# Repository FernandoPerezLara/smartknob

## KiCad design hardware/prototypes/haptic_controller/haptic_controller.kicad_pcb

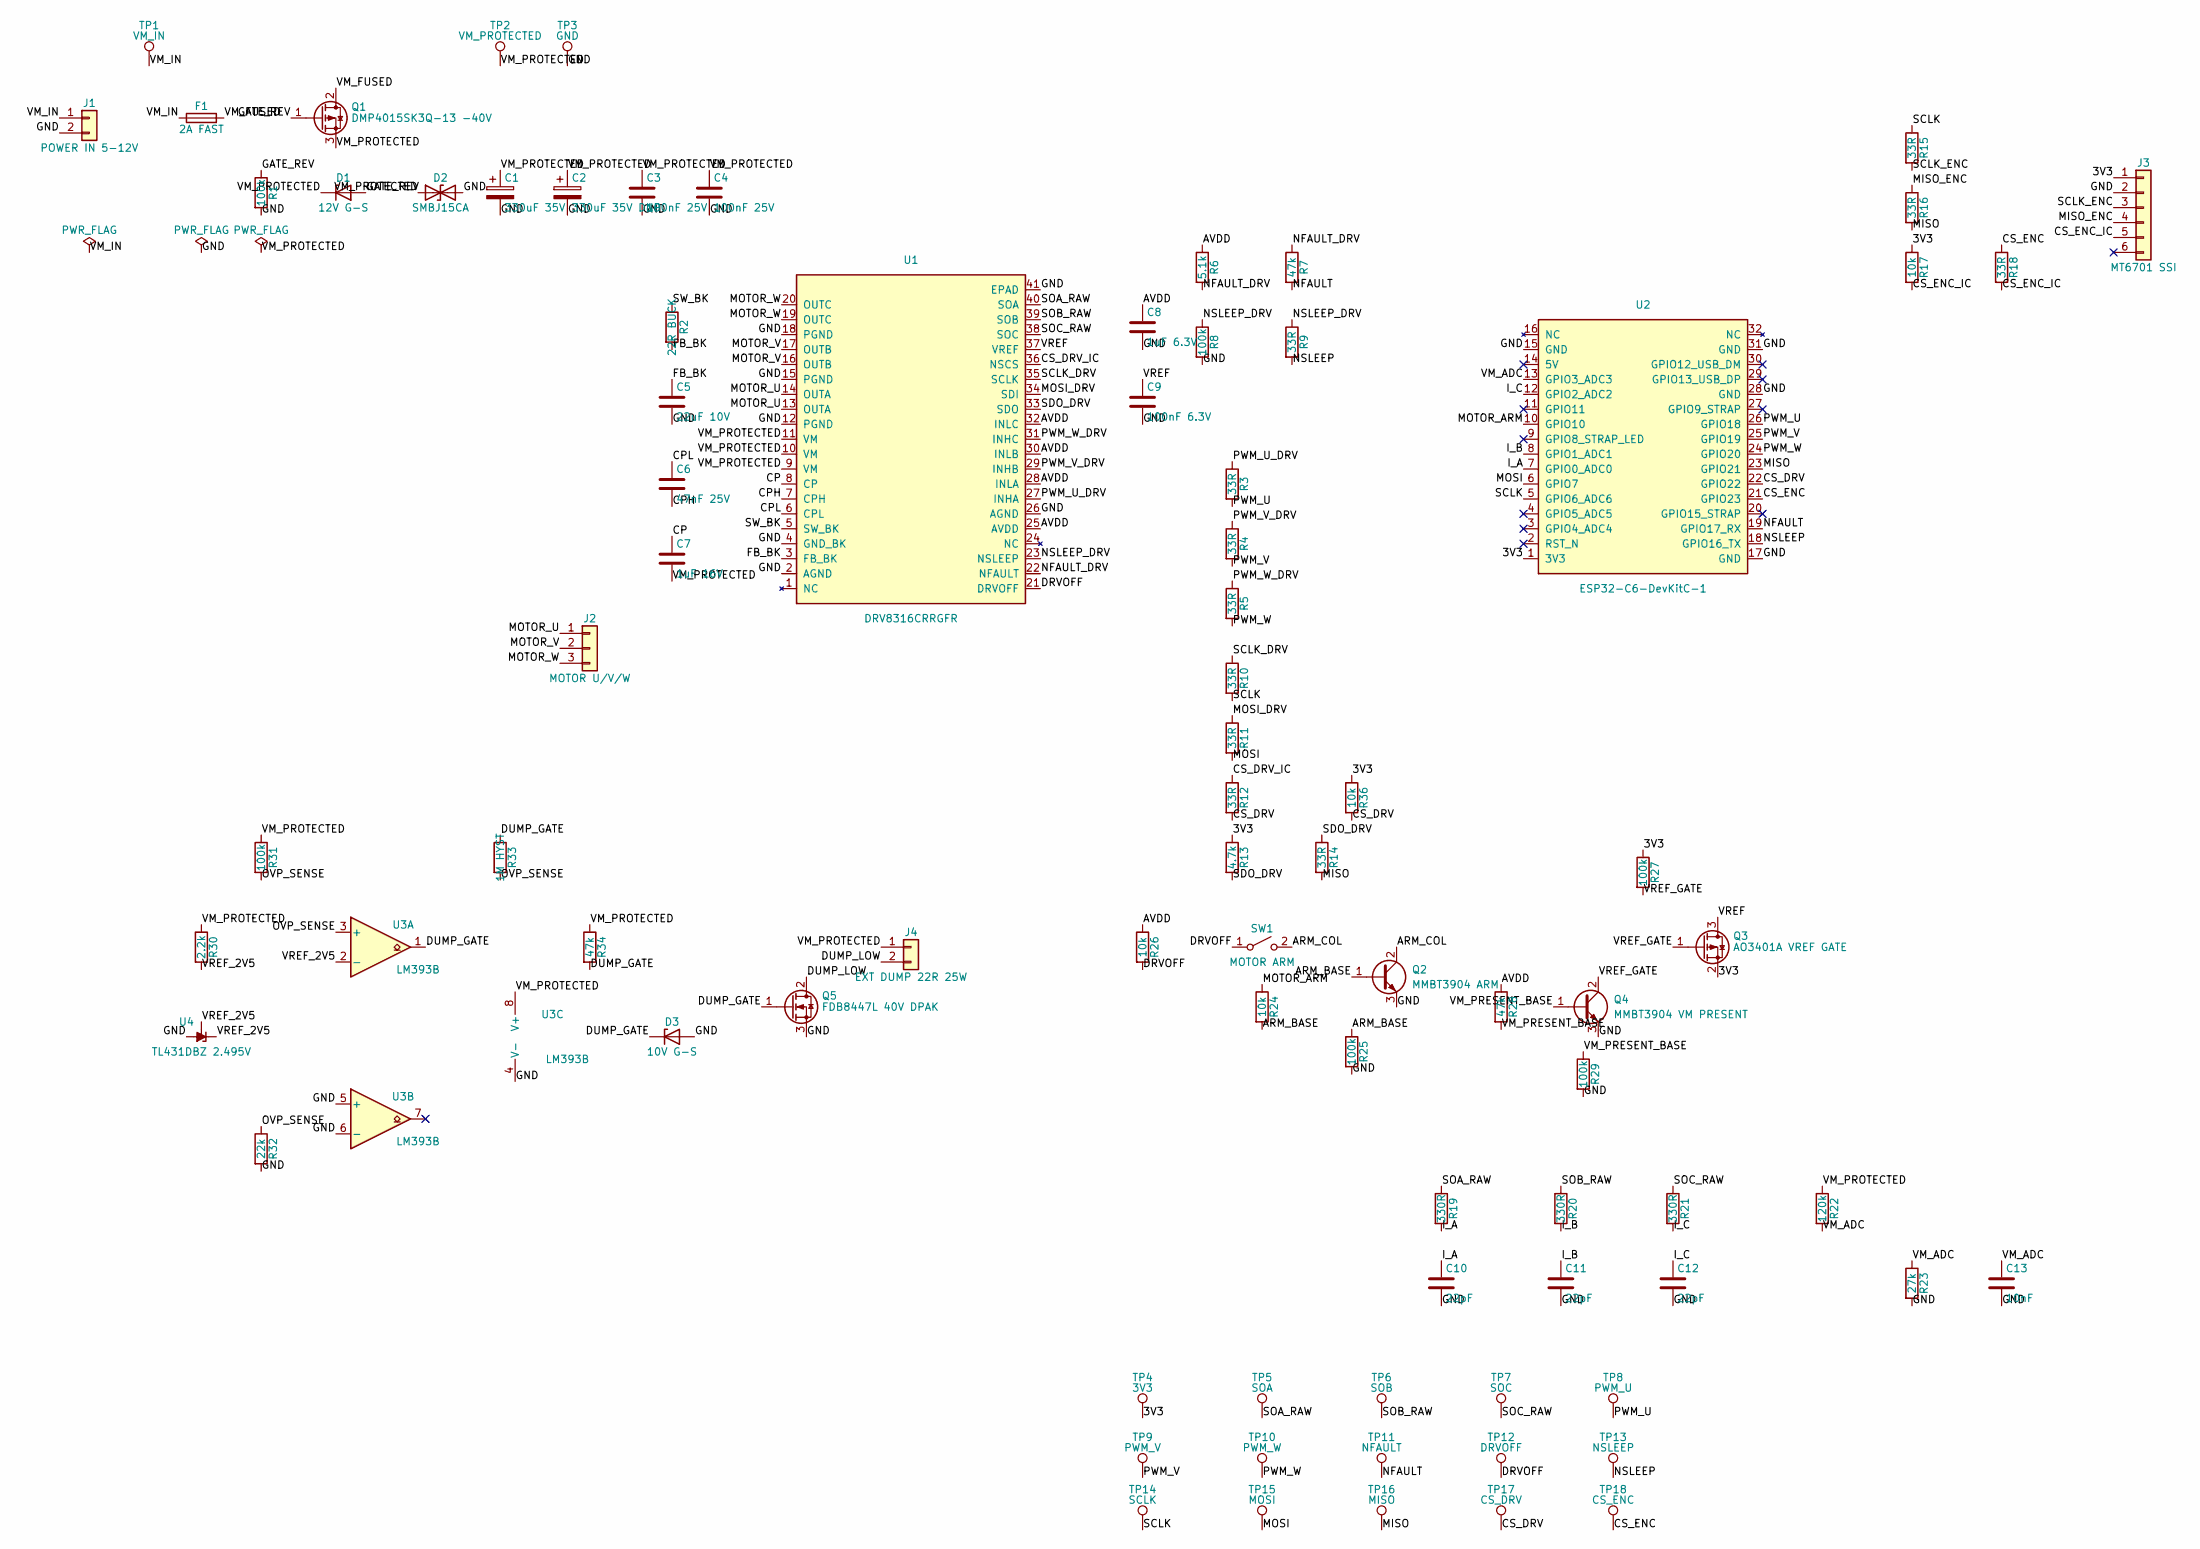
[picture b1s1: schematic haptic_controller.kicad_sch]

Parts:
C1: 330uF 35V; CP_Radial_D10.0mm_P5.00mm
C2: 330uF 35V DNP; CP_Radial_D10.0mm_P5.00mm
C3, C4: 100nF 25V; C_0603_1608Metric_Pad1.08x0.95mm_HandSolder
C5: 22uF 10V; C_0805_2012Metric_Pad1.18x1.45mm_HandSolder
C6: 47nF 25V; C_0603_1608Metric_Pad1.08x0.95mm_HandSolder
C7: 1uF 16V; C_0603_1608Metric_Pad1.08x0.95mm_HandSolder
C8: 1uF 6.3V; C_0603_1608Metric_Pad1.08x0.95mm_HandSolder
C9: 100nF 6.3V; C_0603_1608Metric_Pad1.08x0.95mm_HandSolder
C10, C11, C12: 22pF; C_0603_1608Metric_Pad1.08x0.95mm_HandSolder
C13: 10nF; C_0603_1608Metric_Pad1.08x0.95mm_HandSolder
D1: 12V G-S; D_SOD-123
D2: SMBJ15CA; D_SMA_Handsoldering
D3: 10V G-S; D_SOD-123
F1: 2A FAST; Fuseholder_Cylinder-5x20mm_Schurter_0031_8201_Horizontal_Op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
J1: POWER IN 5-12V; TerminalBlock_Phoenix_MKDS-1,5-2_1x02_P5.00mm_Horizontal
J2: MOTOR U/V/W; TerminalBlock_Phoenix_MKDS-1,5-3_1x03_P5.00mm_Horizontal
J3: MT6701 SSI; PinHeader_1x06_P2.54mm_Vertical
J4: EXT DUMP 22R 25W; TerminalBlock_Phoenix_MKDS-1,5-2_1x02_P5.00mm_Horizontal
Q1: DMP4015SK3Q-13 -40V; TO-252-2
Q2: MMBT3904 ARM; SOT-23
Q3: AO3401A VREF GATE; SOT-23
Q4: MMBT3904 VM PRESENT; SOT-23
Q5: FDB8447L 40V DPAK; TO-252-2
R1, R8, R25, R27, R29, R31: 100k; R_0603_1608Metric_Pad0.98x0.95mm_HandSolder
R2: 22R BUCK; R_0603_1608Metric_Pad0.98x0.95mm_HandSolder
R3, R4, R5, R9, R10, R11, R12, R14, R15, R16, R18: 33R; R_0603_1608Metric_Pad0.98x0.95mm_HandSolder
R6: 5.1k; R_0603_1608Metric_Pad0.98x0.95mm_HandSolder
R7, R28, R34: 47k; R_0603_1608Metric_Pad0.98x0.95mm_HandSolder
R13: 4.7k; R_0603_1608Metric_Pad0.98x0.95mm_HandSolder
R17, R24, R26, R36: 10k; R_0603_1608Metric_Pad0.98x0.95mm_HandSolder
R19, R20, R21: 330R; R_0603_1608Metric_Pad0.98x0.95mm_HandSolder
R22: 120k; R_0603_1608Metric_Pad0.98x0.95mm_HandSolder
R23: 27k; R_0603_1608Metric_Pad0.98x0.95mm_HandSolder
R30: 2.2k; R_0603_1608Metric_Pad0.98x0.95mm_HandSolder
R32: 22k; R_0603_1608Metric_Pad0.98x0.95mm_HandSolder
R33: 1M HYST; R_0603_1608Metric_Pad0.98x0.95mm_HandSolder
SW1: MOTOR ARM; SW_SPST_B3U-1000P
TP1: VM_IN; TestPoint_Plated_Hole_D2.0mm
TP2: VM_PROTECTED; TestPoint_Plated_Hole_D2.0mm
TP3: GND; TestPoint_Plated_Hole_D2.0mm
TP4: 3V3; TestPoint_Plated_Hole_D2.0mm
TP5: SOA; TestPoint_Plated_Hole_D2.0mm
TP6: SOB; TestPoint_Plated_Hole_D2.0mm
TP7: SOC; TestPoint_Plated_Hole_D2.0mm
TP8: PWM_U; TestPoint_Plated_Hole_D2.0mm
TP9: PWM_V; TestPoint_Plated_Hole_D2.0mm
TP10: PWM_W; TestPoint_Plated_Hole_D2.0mm
TP11: NFAULT; TestPoint_Plated_Hole_D2.0mm
TP12: DRVOFF; TestPoint_Plated_Hole_D2.0mm
TP13: NSLEEP; TestPoint_Plated_Hole_D2.0mm
TP14: SCLK; TestPoint_Plated_Hole_D2.0mm
TP15: MOSI; TestPoint_Plated_Hole_D2.0mm
TP16: MISO; TestPoint_Plated_Hole_D2.0mm
TP17: CS_DRV; TestPoint_Plated_Hole_D2.0mm
TP18: CS_ENC; TestPoint_Plated_Hole_D2.0mm
U1: DRV8316CRRGFR; DRV8316C_RGF40_Thermal
U2: ESP32-C6-DevKitC-1; ESP32-C6-DevKitC-1_Socket
U3: LM393B; SO-8_3.9x4.9mm_P1.27mm
U4: TL431DBZ 2.495V; SOT-23

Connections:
/3V3: J3.1, Q3.2 (S), R13.1, R17.1, R27.1, R36.1, TP4.1 (1_1), U2.1 (3V3)
/ARM_BASE: Q2.1 (B), R24.2, R25.1
/ARM_COL: Q2.2 (C), SW1.2 (B)
/AVDD: C8.1, R6.1, R26.1, R28.1, U1.25 (AVDD), U1.28 (INLA), U1.30 (INLB), U1.32 (INLC)
/CP: C7.1, U1.8 (CP)
/CPH: C6.2, U1.7 (CPH)
/CPL: C6.1, U1.6 (CPL)
/CS_DRV: R12.2, R36.2, TP17.1 (1_1), U2.22 (GPIO22)
/CS_DRV_IC: R12.1, U1.36 (NSCS)
/CS_ENC: R18.1, TP18.1 (1_1), U2.21 (GPIO23)
/CS_ENC_IC: J3.5, R17.2, R18.2
/DRVOFF: R26.2, SW1.1 (A), TP12.1 (1_1), U1.21 (DRVOFF)
/DUMP_GATE: D3.1 (K), Q5.1 (G), R33.1, R34.2, U3.1
/DUMP_LOW: J4.2, Q5.2 (D)
/FB_BK: C5.1, R2.2, U1.3 (FB_BK)
/GATE_REV: D1.2 (A), Q1.1 (G), R1.1
/GND: C1.2, C2.2, C3.2, C4.2, C5.2, C8.2, C9.2, C10.2, C11.2, C12.2, C13.2, D2.2 (A2), D3.2 (A), J1.2, J3.2, Q2.3 (E), Q4.3 (E), Q5.3 (S), R1.2, R8.2, R23.2, R25.2, R29.2, R32.2, TP3.1 (1_1), U1.2 (AGND), U1.4 (GND_BK), U1.12 (PGND), U1.15 (PGND), U1.18 (PGND), U1.26 (AGND), U1.41 (EPAD), U2.15 (GND), U2.17 (GND), U2.28 (GND), U2.31 (GND), U3.4 (V-), U3.5 (+), U3.6 (-), U4.3 (A)
/I_A: C10.1, R19.2, U2.7 (GPIO0_ADC0)
/I_B: C11.1, R20.2, U2.8 (GPIO1_ADC1)
/I_C: C12.1, R21.2, U2.12 (GPIO2_ADC2)
/MISO: R14.2, R16.2, TP16.1 (1_1), U2.23 (GPIO21)
/MISO_ENC: J3.4, R16.1
/MOSI: R11.2, TP15.1 (1_1), U2.6 (GPIO7)
/MOSI_DRV: R11.1, U1.34 (SDI)
/MOTOR_ARM: R24.1, U2.10 (GPIO10)
/MOTOR_U: J2.1, U1.13 (OUTA), U1.14 (OUTA)
/MOTOR_V: J2.2, U1.16 (OUTB), U1.17 (OUTB)
/MOTOR_W: J2.3, U1.19 (OUTC), U1.20 (OUTC)
/NFAULT: R7.2, TP11.1 (1_1), U2.19 (GPIO17_RX)
/NFAULT_DRV: R6.2, R7.1, U1.22 (NFAULT)
/NSLEEP: R9.2, TP13.1 (1_1), U2.18 (GPIO16_TX)
/NSLEEP_DRV: R8.1, R9.1, U1.23 (NSLEEP)
/OVP_SENSE: R31.2, R32.1, R33.2, U3.3 (+)
/PWM_U: R3.2, TP8.1 (1_1), U2.26 (GPIO18)
/PWM_U_DRV: R3.1, U1.27 (INHA)
/PWM_V: R4.2, TP9.1 (1_1), U2.25 (GPIO19)
/PWM_V_DRV: R4.1, U1.29 (INHB)
/PWM_W: R5.2, TP10.1 (1_1), U2.24 (GPIO20)
/PWM_W_DRV: R5.1, U1.31 (INHC)
/SCLK: R10.2, R15.1, TP14.1 (1_1), U2.5 (GPIO6_ADC6)
/SCLK_DRV: R10.1, U1.35 (SCLK)
/SCLK_ENC: J3.3, R15.2
/SDO_DRV: R13.2, R14.1, U1.33 (SDO)
/SOA_RAW: R19.1, TP5.1 (1_1), U1.40 (SOA)
/SOB_RAW: R20.1, TP6.1 (1_1), U1.39 (SOB)
/SOC_RAW: R21.1, TP7.1 (1_1), U1.38 (SOC)
/SW_BK: R2.1, U1.5 (SW_BK)
/VM_ADC: C13.1, R22.2, R23.1, U2.13 (GPIO3_ADC3)
/VM_FUSED: F1.2, Q1.2 (D)
/VM_IN: F1.1, J1.1, TP1.1 (1_1)
/VM_PRESENT_BASE: Q4.1 (B), R28.2, R29.1
/VM_PROTECTED: C1.1, C2.1, C3.1, C4.1, C7.2, D1.1 (K), D2.1 (A1), J4.1, Q1.3 (S), R22.1, R30.1, R31.1, R34.1, TP2.1 (1_1), U1.9 (VM), U1.10 (VM), U1.11 (VM), U3.8 (V+)
/VREF: C9.1, Q3.3 (D), U1.37 (VREF)
/VREF_2V5: R30.2, U3.2 (-), U4.1 (K), U4.2 (REF)
/VREF_GATE: Q3.1 (G), Q4.2 (C), R27.2

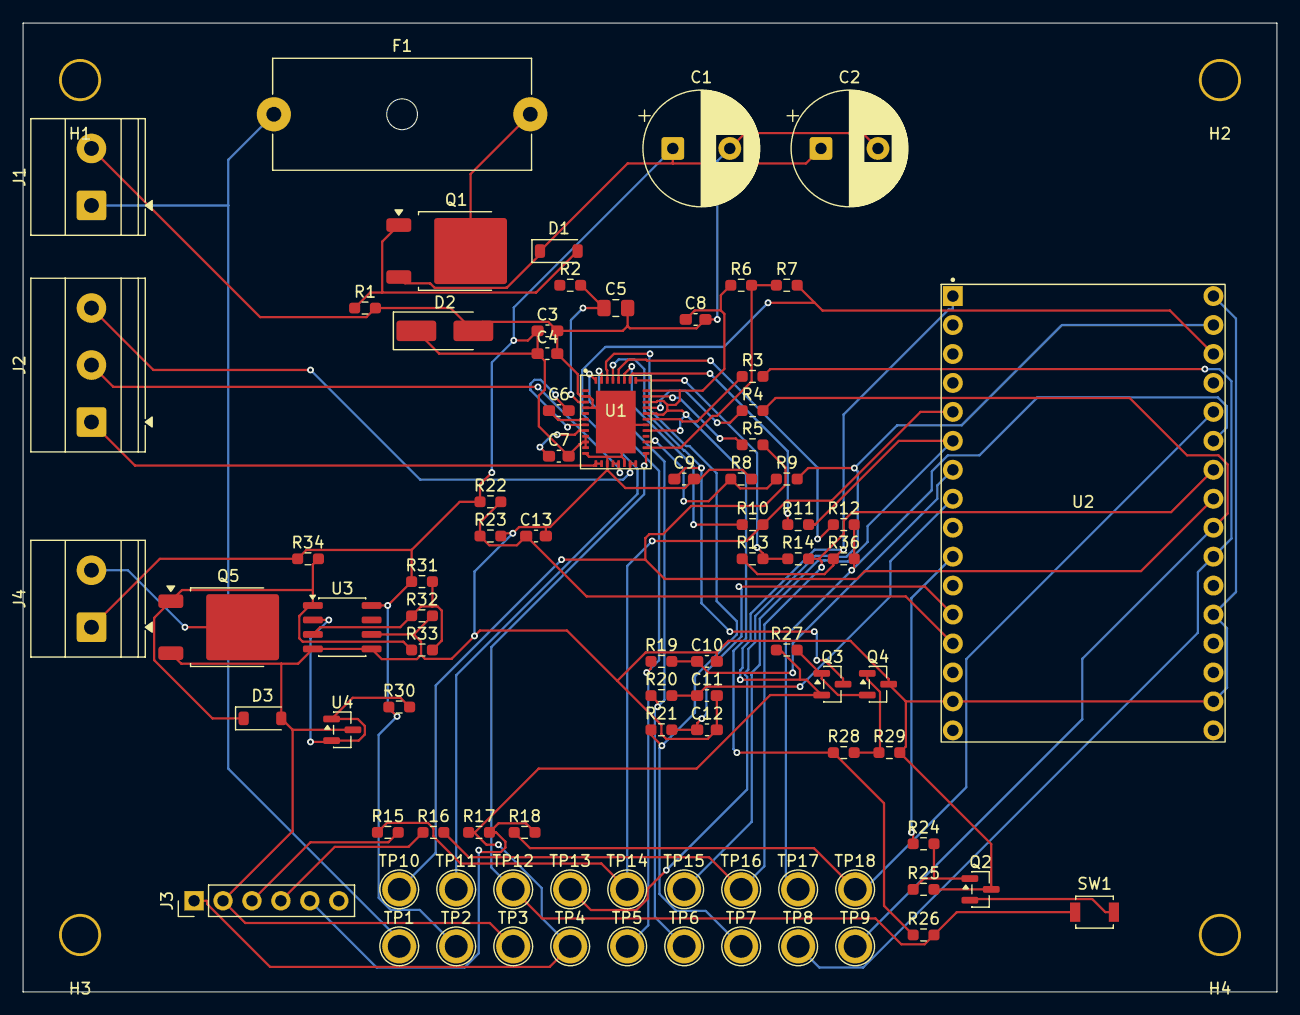
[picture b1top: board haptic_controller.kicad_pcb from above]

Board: 2 copper layers, 110.0 x 85.0 mm, 88 parts (0 on the bottom side), 55 nets.

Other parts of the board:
H1, H2, H3, H4: MountingHole; MountingHole_3.2mm

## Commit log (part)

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2025-08-07 chore: hello code
2025-08-07 chore: create project
2025-08-11 feat: add spi communication with peripheral device
2025-08-12 feat: consolidate error handling into unified SmartknobError
2025-08-18 feat: implement GCA901 display driver
2025-08-19 feat: optimizing display buffer
2025-08-19 feat: improve display subsystem with better error handling
2025-08-19 feat: pptimize display driver to use static data buffers
2025-08-20 refactor: use write_data method for SPI operations
    Replace direct SPI write calls with the existing write_data helper
    method in set_pixel and fill_screen functions to improve code
    consistency and maintainability. This change ensures all data writes go
    through the same code path and maintains proper DC pin state management.
2025-08-20 feat: add line drawing functionality
    Implement Bresenham's line algorithm for drawing lines on the display.
    The draw_line method takes start/end coordinates and color, using an
    efficient integer-only algorithm to draw pixels along the line path.
2025-08-21 refactor: extract graphics functionality into separate module
    Move pixel, background, line, and circle drawing methods from mod.rs to
    a dedicated graphics.rs module to improve code organization. Also expose
    write_data, sleep, wake, and set_frame methods as public to support the
    extracted graphics functionality.
2025-08-22 chore: move display CS definition
2025-08-26 refactor: clean up import paths and remove dead code
    Standardize import paths to use relative imports instead of absolute
    crate paths for better module organization. Remove empty impl block for
    HardwareError.
2025-08-26 feat: implement trait-based graphics primitives system
    Replace direct Display drawing methods with trait-based graphics system.
    Creates Figure trait and struct-based primitives (Line, Circle) for
    better code organization and extensibility. Updates app module to use
    new graphics API with constructor pattern.
    - Add Figure trait for drawable graphics primitives - Convert draw_line
    and draw_circle methods to Line and Circle structs - Implement Figure
2025-09-01 refactor: simplify primitives API and improve display integration
2025-09-02 feat: add DMA support to SPI interface
    Add Direct Memory Access (DMA) support to the SPI hardware interface to
    improve performance for large data transfers. This enhancement reduces
    CPU overhead by allowing the DMA controller to handle data transfers
    directly between memory and SPI peripherals.
    - Update SPI interface to use SpiDmaBus instead of basic Spi - Configure
    DMA buffers with 32KB capacity for both RX and TX - Add DMA channel
2025-09-04 chore: add .claude directory to gitignore
2025-09-04 chore: add Docker development environment setup
    Add Docker configuration files to enable containerized development and
    CI workflows for the embedded Rust project.
2025-09-04 chore: rename CI workflow
2025-09-12 feat: upgrade ESP-HAL dependencies and enhance embedded development configuration
    Update ESP-HAL ecosystem to latest versions from main branch for
    improved hardware abstraction and performance. Add heap allocation
    support via esp-alloc and configure enhanced logging capabilities.
    Key changes: - Migrate ESP-HAL dependencies to git main branch for
    latest features - Enable heap allocation with esp-alloc integration -
    Configure ESP logging environment and enhanced build standards - Update
2025-09-13 fix: optimize SPI and memory settings for display
    Adjust SPI clock to 80MHz, reduce DMA buffer size to 4KB, and set heap
    size to match display requirements (240x240x2 bytes)
2025-09-15 feat(display): add RGB color system and refactor graphics primitives
    Replace raw u16 color values with a new Color struct that provides RGB
    color representation and conversion utilities. This improves code
    readability and maintainability by using semantic color values instead
    of hex color codes.
    - Add Color struct with RGB components and conversion methods - Update
    FilledCircle to use Color instead of u16 - Add clear_color method to
2025-09-16 feat(display): add text rendering support
    Add text rendering capabilities to the graphics system by implementing a
    new Text struct that supports configurable alignment and positioning.
    - Add Text graphics primitive with alignment, color, and positioning
    support - Rename Figure trait to Graphic for better naming consistency -
    Integrate text rendering into the main app animation loop - Increase
    heap allocator size to accommodate text rendering operations
2025-09-17 feat: create views structure
2025-09-18 feat(ui): add len and is_empty methods to ViewManager
2025-09-18 chore: reorganize imports and update rustfmt configuration
    Update rustfmt.toml to use StdExternalCrate import grouping and
    Crate-level granularity with alphabetical reordering. Reorganize all
    import statements across the codebase to follow the new formatting
    standards, grouping standard library imports first, then external
    crates, then local crate imports.
2025-09-30 feat(macros): add helper macro for including generated files
    Introduce include_generated! macro that simplifies including files from the OUT_DIR during build time. The macro provides two variants: one for including binary data (bytes) and one for including tex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
2025-09-30 refactor(build): reorganize build script into modular structure
    Move linker argument from build.rs to cargo config and restructure build
    scripts into a dedicated build/ directory with separate modules for
    different asset types. The FontBuilder implements a new AssetBuilder
    trait to enable extensible build-time asset generation.
    This change improves build script organization and makes it easier to
    add new build-time asset processors in the future.
2025-09-30 refactor(build): consolidate asset builders into assets module
    Move builder trait and font builder into a dedicated assets module for
    better organization. The AssetBuilder trait and FontBuilder
    implementation are now under build/assets/ instead of separate files at
    the build root level.
2025-10-01 refactor(ci): migrate workflows to use Just and split lint into format/check
    Replace direct cargo commands with Just recipes across Docker and CI
    workflows. Split the monolithic lint workflow into separate format and
    check workflows to improve clarity and allow independent execution.
    Update Dockerfile to install Just and copy justfile configuration.
    Changes include: - Add Just installation to Dockerfile - Replace cargo
    commands with Just recipes in docker-compose.yml - Split lint.yml into
2025-10-07 feat(build): implement packed binary font format with 4-bit antialiasing
    Replace placeholder font output with a custom binary format that packs glyph data efficiently for embedded systems. The format includes a header with character count and baseline metrics, a sorted ch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
    This reduces memory footprint compared to full 8-bit alpha values while maintaining acceptable rendering quality for embedded displays.
2025-10-08 chore(text): load new font
2025-10-10 refactor(graphics)add error handling to graphics rendering pipeline
    Introduce GraphicsError type and propagate errors through the entire graphics rendering chain. Previously, drawing operations silently ignored errors using 'let _ = ...' patterns, which could lead to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
    This change makes the Graphic trait's draw method fallible, requiring all implementations to return Result<(), GraphicsError>. The error type includes proper variant for invalid font data validation.
    Key changes:
    - Add GraphicsError enum with Display and From trait implementations
    - Make Graphic::draw() return Result<(), GraphicsError>
    - Add BinaryFont::new() with validation for font data inte
2025-10-12 refactor(fonts): remove unused baseline field and optimize text rendering
    Remove the max_baseline field from the binary font format as it was calculated but never actually used in the text rendering logic. This simplifies the font file structure and reduces file size.
    Additionally, extract RGB565 alpha blending logic into a dedicated blend_rgb565 function to improve code readability and reusability. Minor optimization using bitwise AND for even/odd pixel index che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
    BREAKING CHANGE: Binary font file format has changed. Font files must be regenerated with the updated build script.
2025-10-12 fix: add ldproxy
2025-10-12 chore(spi): remove frequency bounds check in SPI initialization
2025-10-22 refactor(spi): remove frequency parameter from SpiDevice
    Remove per-device frequency configuration from SpiDevice as frequency is configured at the bus level during SharedSpiBus initialization. This simplifies the device creation API and prevents redundant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
    Also rename SharedSpiBus::as_ref() to bus() for better clarity and update Display to use SpiDevice directly.
2025-10-22 refactor(spi): move configuration from bus to device level
    Move SPI frequency and mode parameters from SharedSpiBus initialization to individual SpiDevice creation. This allows each device on the shared bus to configure its own frequency and mode settings, a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
    The display now operates at 80MHz while the encoder runs at 1Mhz, optimizing performance for each peripheral's requirements.
2025-10-23 refactor: show status and angle
2025-10-23 feat(display): add advance width support for text rendering
    Add advance_width field to font glyph metadata to properly handle
    character spacing. The advance width determines how far to move the
    cursor after rendering each character, which is essential for correct
    text layout.
    Changes: - Update binary font format to include advance_width in glyph
    metadata (7 bytes instead of 6) - Store advance_width during font asset
2025-10-25 fix(display): correct vertical text alignment baseline calculation
    The previous vertical alignment logic only used glyph height, which
    didn't account for the baseline offset (ymin). This caused text to be
    misaligned vertically, especially for glyphs with descenders or varying
    baseline positions.
    This commit tracks both the maximum top position and minimum bottom
    position of glyphs, then uses these values to properly calculate the
2025-10-25 feat: add code of conduct
2025-10-25 feat: add security guidelines
2025-10-25 chore: improve bug report issue template
2025-10-25 fix: use literal bug emoji in bug report template
2025-10-25 Use warning admonition in bug report template
2025-10-25 fix: move issue search tip into markdown block
2025-10-25 feat: add feature request issue template
2025-10-29 refactor: restructure project to isolate firmware in dedicated subdirectory
    Move all Rust firmware code, configuration, and build files into a
    dedicated firmware/ directory to better organize the repository for
    future expansion with additional components (e.g., hardware designs,
    documentation, companion applications).
    Update CI workflows to set working-directory to firmware/ for all
    Docker-based build, check, and format jobs. Update CONTRIBUTING.md and
2025-10-29 feat(hardware): add initial KiCad project files
    Initialize hardware design directory with KiCad v9.0 project structure
    including schematic, PCB layout, and project configuration files. This
    establishes the foundation for the smartknob hardware design.
2026-01-01 feat(firmware): add circular position indicator to display
    Replace angle-based position tracking with percentage-based system
    (0-100%). Add visual feedback with a white circular indicator that
    rotates around the display center based on encoder position. The
    indicator uses trigonometric calculations to compute X/Y coordinates
    from the encoder angle.
    Changes include:
